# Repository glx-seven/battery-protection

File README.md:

# Battery protection PCB
A protection PCB for small LiPo cells, I did design it for use with cells extracted from these disposable vapes I had found a few laying around in the city I live.

It is designed to be a flex-PCB, also it can technically be cut down to use it with small square cells with the pads  on the back.

I have attached gerber files so you can order it at your favourite PCB-manufacturer, I did use JLCPCB's flex-PCBs and they came out nicely.

The N-FETs used are probably a litte oversized but I used them because I had them on hand and they have a low Vgs and low Rds(on). Feel free to use different/cheaper ones, that's why I uploades all the source files.

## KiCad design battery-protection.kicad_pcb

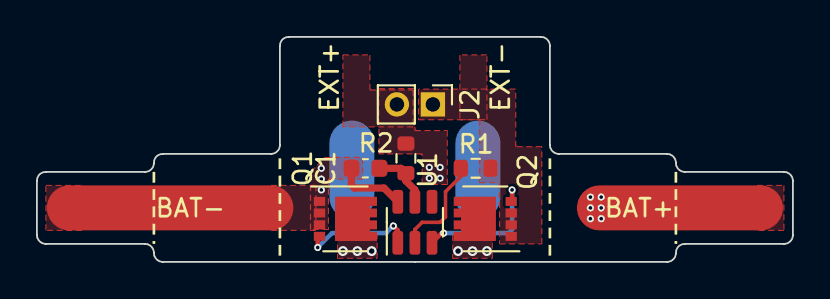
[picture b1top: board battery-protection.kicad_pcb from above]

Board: 2 copper layers, 42.0 x 12.5 mm, 7 parts (0 on the bottom side), 8 nets.

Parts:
C1: 100n; C_0603_1608Metric
J2: Conn_01x02_Pin; PinHeader_1x02_P2.00mm_Vertical
Q1, Q2: GSFN2306; VSON-8_3.3x3.3mm_P0.65mm_NexFET
R1: 2k; R_0603_1608Metric
R2: 470R; R_0603_1608Metric
U1: S-8261AAJMD-G2JT2G; TSOT-23-6

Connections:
/BAT+: J2.2, R2.1
/BAT-: C1.2, Q1.1 (S), Q1.2 (S), Q1.3 (S), U1.6 (VSS)
/CO: Q2.4 (G), U1.3 (CO)
/DO: Q1.4 (G), U1.1 (DO)
/EXT-: J2.1, Q2.1 (S), Q2.2 (S), Q2.3 (S), R1.2
/FET_CON: Q1.5 (D), Q2.5 (D)
/VM: R1.1, U1.2 (VM)
unnamed: C1.1, R2.2, U1.5 (VDD)

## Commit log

2023-11-05 Initial release
2023-11-05 Added picture
